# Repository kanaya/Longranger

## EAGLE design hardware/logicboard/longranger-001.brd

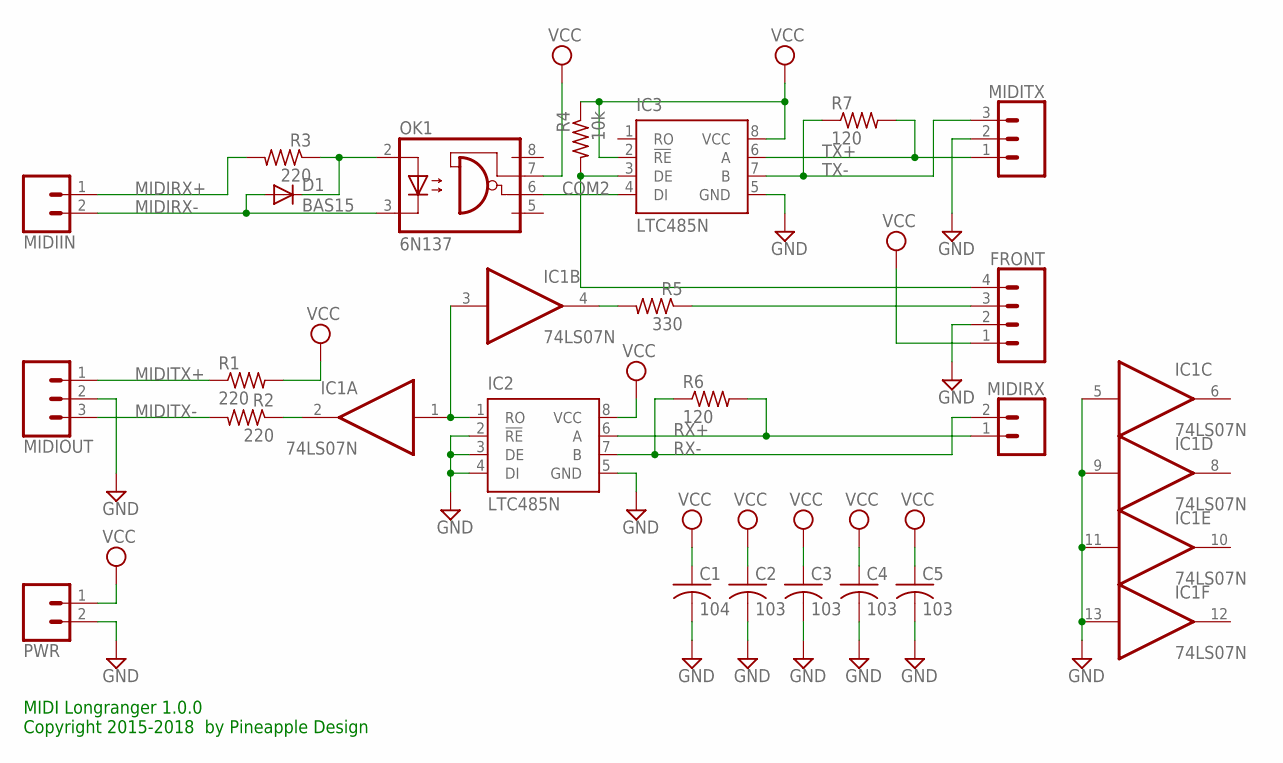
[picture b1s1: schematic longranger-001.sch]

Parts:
C1: 104; C025-025X050
C2, C3, C4, C5: 103; C025-025X050
D1: BAS15; DO34-7
FRONT: CONN_04JST-PTH; JST-4-PTH
IC1: 74LS07N; DIL14
IC2, IC3: LTC485N; DIL08
MIDIIN: CONN_02JST-PTH-2; JST-2-PTH
MIDIOUT: CONN_03JST-PTH; JST-3-PTH
MIDIRX: CONN_02JST-PTH-2; JST-2-PTH
MIDITX: CONN_03JST-PTH; JST-3-PTH
OK1: 6N137; DIL08
PWR: CONN_02JST-PTH-2; JST-2-PTH
R1, R2, R3: 220; 0204/5
R4: 10k; 0204/5
R5: 330; 0204/5
R6, R7: 120; 0204/5

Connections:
COM1: IC1.1 (I), IC1.3 (I), IC2.1 (RO)
COM2: IC3.4 (DI), OK1.6 (VO)
GND: C1.2, C2.2, C3.2, C4.2, C5.2, FRONT.2, IC1.5 (I), IC1.7 (GND), IC1.9 (I), IC1.11 (I), IC1.13 (I), IC2.2 (!RE), IC2.3 (DE), IC2.4 (DI), IC2.5 (GND), IC3.5 (GND), MIDIOUT.2, MIDITX.2, PWR.2
INDICATOR: FRONT.3, R5.1
MIDIRX+: MIDIIN.1, R3.2
MIDIRX-: D1.A, MIDIIN.2, OK1.3 (C)
MIDITX+: MIDIOUT.1, R1.1
MIDITX-: MIDIOUT.3, R2.2
MUTE: FRONT.4, IC3.3 (DE), R4.2
unnamed: IC1.2 (O), R2.1
unnamed: IC1.4 (O), R5.2
unnamed: D1.C, OK1.2 (A), R3.1
RX+: IC2.6 (A), MIDIRX.1, R6.2
RX-: IC2.7 (B), MIDIRX.2, R6.1
TX+: IC3.6 (A), MIDITX.1, R7.2
TX-: IC3.7 (B), MIDITX.3, R7.1
VCC: C1.1, C2.1, C3.1, C4.1, C5.1, FRONT.1, IC1.14 (VCC), IC2.8 (VCC), IC3.2 (!RE), IC3.8 (VCC), OK1.7 (VE), PWR.1, R1.2, R4.1

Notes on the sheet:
MIDI Longranger 1.0.0 Copyright 2015-2018 by Pineapple Design

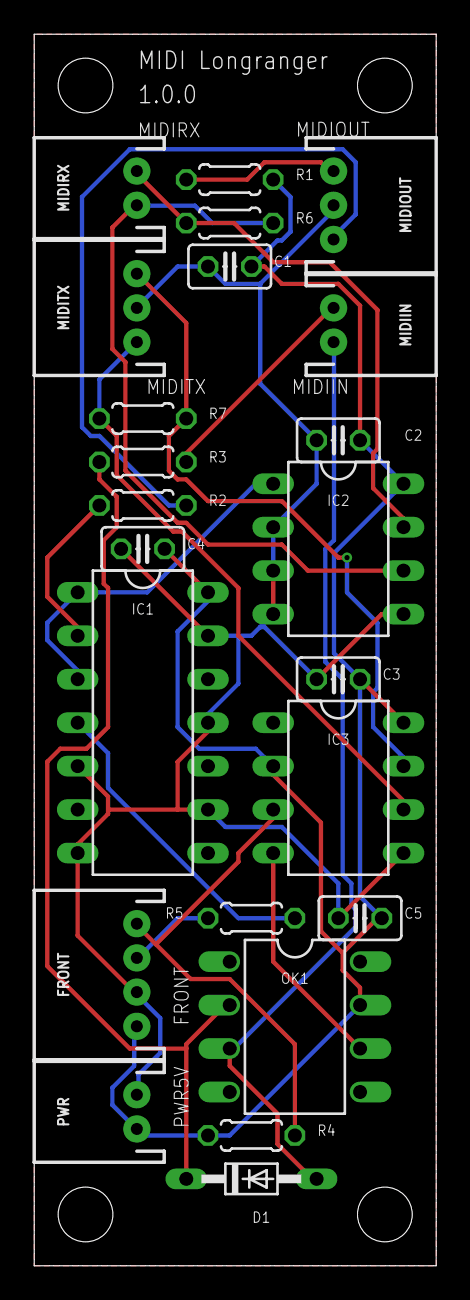
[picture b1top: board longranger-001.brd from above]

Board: 2 copper layers, 23.5 x 72.0 mm, 23 parts (0 on the bottom side), 17 nets.

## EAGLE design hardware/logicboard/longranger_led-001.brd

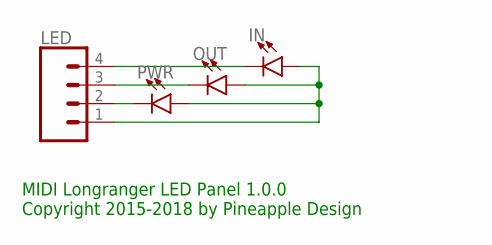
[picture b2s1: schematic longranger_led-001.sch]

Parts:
IN: LED3MM; LED_3MM
LED: CONN_04JST-PTH-VERT; JST-4-PTH-VERT
OUT: LED3MM; LED_3MM
PWR: LED3MM; LED_3MM

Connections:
unnamed: LED.2, PWR.K (C)
unnamed: LED.3, OUT.K (C)
unnamed: IN.K (C), LED.4
PWR: IN.A, LED.1, OUT.A, PWR.A

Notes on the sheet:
MIDI Longranger LED Panel 1.0.0 Copyright 2015-2018 by Pineapple Design

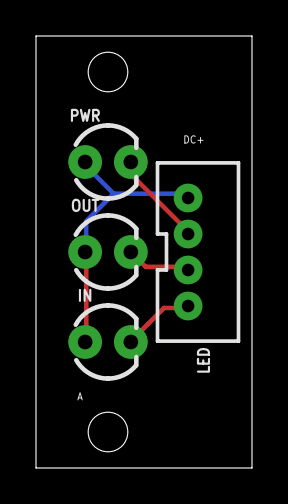
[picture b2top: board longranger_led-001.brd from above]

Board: 2 copper layers, 12.0 x 24.0 mm, 4 parts (0 on the bottom side), 4 nets.

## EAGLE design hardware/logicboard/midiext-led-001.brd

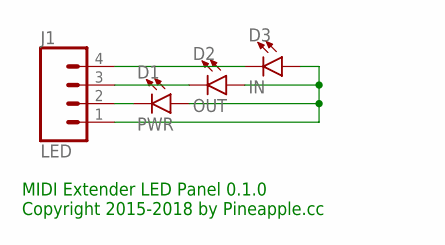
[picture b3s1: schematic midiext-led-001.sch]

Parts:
D1: PWR; LED_3MM
D2: OUT; LED_3MM
D3: IN; LED_3MM
J1: LED; JST-4-PTH-VERT

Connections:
unnamed: D1.A, D2.A, D3.A, J1.1
unnamed: D1.K (C), J1.2
unnamed: D2.K (C), J1.3
unnamed: D3.K (C), J1.4

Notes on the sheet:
MIDI Extender LED Panel 0.1.0 Copyright 2015-2018 by Pineapple.cc

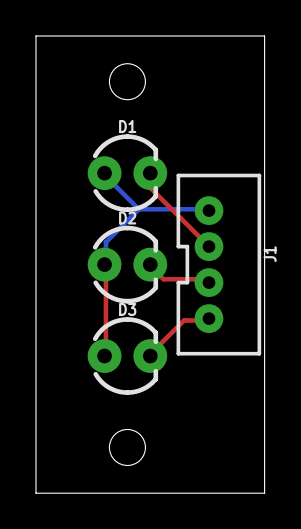
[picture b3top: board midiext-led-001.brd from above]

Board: 2 copper layers, 12.7 x 25.4 mm, 4 parts (0 on the bottom side), 4 nets.

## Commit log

2013-11-09 schematic.
2013-11-10 product photo.
2018-02-15 Roughly imported from Pineapple II design.
2018-02-15 New schematic.
2018-02-15 Changed connectors.
2018-02-15 Now has LED indicator port.
2018-02-15 Now has LED indicator panel.
2018-02-17 First try.
2018-02-17 Second try.
2018-02-17 Drill holese.
2018-02-17 Imported panel AI files from Pineapple II.
2018-02-17 Panels.
2018-02-17 Removed LED panel from main logic board.
2018-02-17 LED panel board.
2018-02-17 Fixed a minor error of the front panel.
2018-02-18 Fixed values.
2018-02-20 No change.
2018-02-20 Renumbered components.
2018-02-28 Changed layout.
2018-02-28 Changed silk pattern.
2018-02-28 Name change.
2018-03-01 Changed copyright notice.
2018-03-02 Changed LED pitch.
2018-03-02 P-ban.
2018-03-02 Layout.
2018-03-05 Renew.
2018-03-10 P-ban ready.
2018-03-10 Removed LED panel.
2018-03-10 New panel.
2018-03-10 Refined the front panel.
2018-03-10 Refined the back panel.
2018-03-10 Refined another version of back panel.
2018-03-10 Moved back panel to MIDI-Panel repo.
2018-03-12 Changed panel design.
2018-03-12 New front panel.
2018-03-12 Ultra slim logicboard. Needs to refine silk pattern.
2018-03-12 New logic board. Everything is ready.
2018-03-12 Changed signal name.
2018-03-16 Fixed error.

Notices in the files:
parts and their libraries:
SparkFun-Connectors: Licensing: Creative Commons ShareAlike 4.0 International - https://creativecommons.org/licenses/by-sa/4.0
